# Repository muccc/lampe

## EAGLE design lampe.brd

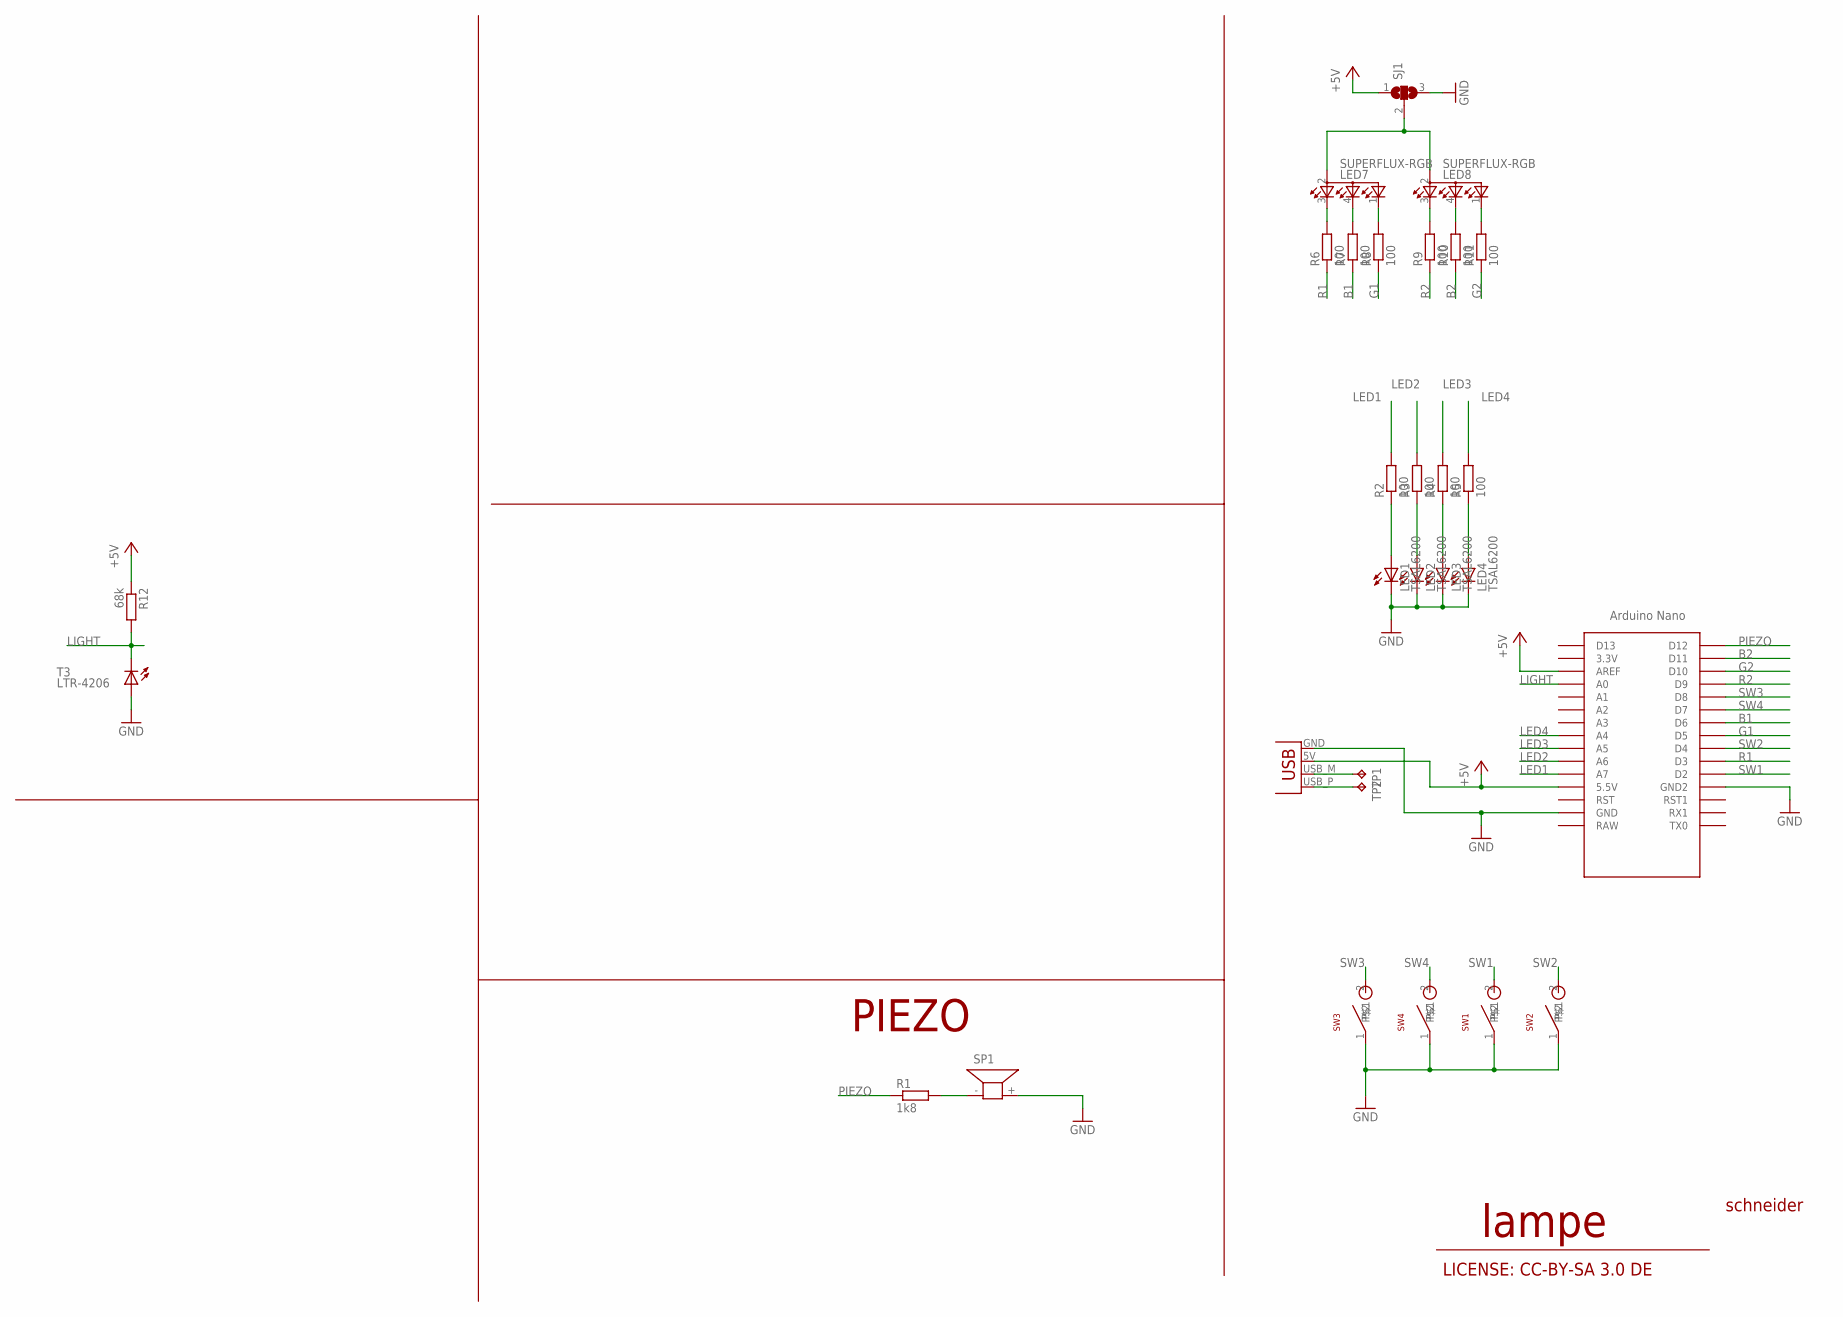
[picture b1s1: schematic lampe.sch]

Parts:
LED1, LED2, LED3, LED4: TSAL6200; LED5MM
LED7, LED8: SUPERFLUX-RGB; SUPERFLUX-7.6X7.6
R1: 1k8; 0207/7
R2, R3, R4, R5, R6, R7, R8, R9, R10, R11: 100; 0207/7
R12: 68k; 0207/7
SJ1: SJ2W; SJ_2
SP1: AL11P
SW1, SW2, SW3, SW4: SWITCH
T3: LTR-4206; LED3MM
TP1, TP2: TPB1,27; B1,27
U$1: NANO
X1: USBPCB; USB-A-PCB

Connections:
+5V: R12.1, SJ1.1, U$1.5V (5.5V), U$1.AREF, X1.5V (VBUS)
B1: R7.1, U$1.D6
B2: R10.1, U$1.D11
G1: R8.1, U$1.D5
G2: R11.1, U$1.D10
GND: LED1.K (C), LED2.K (C), LED3.K (C), LED4.K (C), SJ1.3, SP1.+ (2), SW1.1, SW2.1, SW3.1, SW4.1, T3.A, U$1.GND, U$1.GND1 (GND2), X1.GND
LED1: R2.2, U$1.A7
LED2: R3.2, U$1.A6
LED3: R4.2, U$1.A5
LED4: R5.2, U$1.A4
LIGHT: R12.2, T3.K (C), U$1.A0
unnamed: LED2.A, R3.1
unnamed: LED7.3 (CRED), R6.2
unnamed: LED3.A, R4.1
unnamed: LED7.4 (CBLUE), R7.2
unnamed: LED7.1 (CGREEN), R8.2
unnamed: LED8.3 (CRED), R9.2
unnamed: LED8.4 (CBLUE), R10.2
unnamed: LED8.1 (CGREEN), R11.2
unnamed: LED7.2 (A2), LED8.2 (A2), SJ1.2
unnamed: LED4.A, R5.1
unnamed: TP1.TP, X1.USB_M (D-)
unnamed: TP2.TP, X1.USB_P (D+)
unnamed: LED1.A, R2.1
unnamed: R1.2, SP1.- (1)
PIEZO: R1.1, U$1.D12
R1: R6.1, U$1.D3
R2: R9.1, U$1.D9
SW1: SW1.2, U$1.D2
SW2: SW2.2, U$1.D4
SW3: SW3.2, U$1.D8
SW4: SW4.2, U$1.D7

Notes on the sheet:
schneider
lampe
LICENSE: CC-BY-SA 3.0 DE
PIEZO

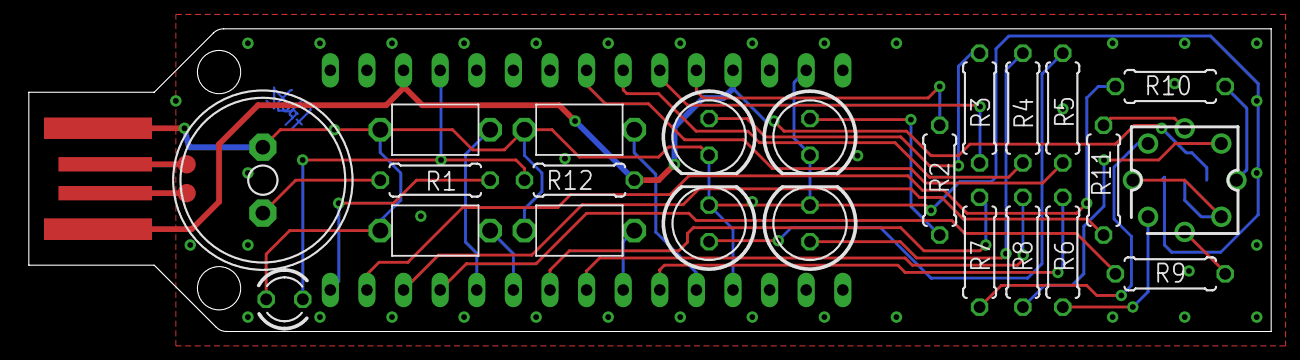
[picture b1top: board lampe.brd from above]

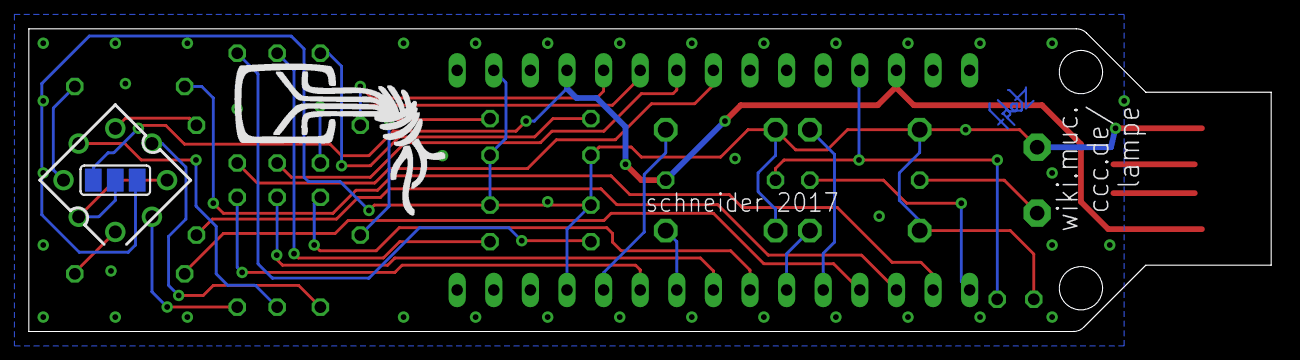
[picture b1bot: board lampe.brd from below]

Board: 2 copper layers, 86.2 x 21.0 mm, 29 parts (3 on the bottom side), 32 nets.

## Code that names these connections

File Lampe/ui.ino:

#define LED1  A3
#define LED2  A5
#define LED3  A2
#define LED4  A4

#define BUTTON1 2
#define BUTTON2 4
#define BUTTON3 8
#define BUTTON4 7

int ui_init(void)
{
  pinMode(LED1, OUTPUT);
  pinMode(LED2, OUTPUT);
  pinMode(LED3, OUTPUT);
  pinMode(LED4, OUTPUT);

  pinMode(BUTTON1, INPUT_PULLUP);
  pinMode(BUTTON2, INPUT_PULLUP);
  pinMode(BUTTON3, INPUT_PULLUP);
  pinMode(BUTTON4, INPUT_PULLUP);
}

void ui_setLed(int led, int an)
{
  if(led == 1) {
    if(an) {
      digitalWrite(LED1, HIGH);
    } else {
      digitalWrite(LED1, LOW);
    }
  }
  if(led == 2) {
    if(an) {
      digitalWrite(LED2, HIGH);
    } else {
      digitalWrite(LED2, LOW);
    }
  }
  if(led == 3) {
    if(an) {
      digitalWrite(LED3, HIGH);
    } else {
      digitalWrite(LED3, LOW);
    }
  }
  if(led == 4) {
    if(an) {
      digitalWrite(LED4, HIGH);
    } else {
      digitalWrite(LED4, LOW);
    }
  }
}

int ui_isPressed(int button)
{
  if(button == 1) {
    if(digitalRead(BUTTON1) == LOW) {
      return 1;
    }
  }
  if(button == 2) {
    if(digitalRead(BUTTON2) == LOW) {
      return 1;
    }
  }
  if(button == 3) {
    if(digitalRead(BUTTON3) == LOW) {
      return 1;
    }
  }
  if(button == 4) {
    if(digitalRead(BUTTON4) == LOW) {
      return 1;
    }
  }
  return 0;
}

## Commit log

2017-07-05 add component libraries
2017-07-05 update silk screen, add usb connector
2017-07-20 chore(eagle): Add design rules file
2017-07-20 feat(lampe): Fix silk screen and some values
2017-07-23 feat(arduino): Basic arduino example
2017-07-23 fix(arduino): Remove broken file header
2017-07-24 fix(arduino): Adapt to reality
2017-07-24 lampe an / lampe aus.
2017-07-24 debug
2017-07-24 minimal kommentiert
2017-07-24 Release of Lampe-Arduino-Software
